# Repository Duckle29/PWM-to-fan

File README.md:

# PWM-to-fan

This is a small board intended to take an open-drain inverted PWM output, and convert it to constant current from 0-200mA for a fan. 
This is because many fans do not run well with their main supply PWMed. The reason to go for Constant current, is to limit the heat wasted in the transistor.

The board was made for use with the Duet 3D printer controllers, but will work for any open-drain inverted PWM outputs.

Many thanks to [N2](http://ee.david.promo) who came up with the circuit.

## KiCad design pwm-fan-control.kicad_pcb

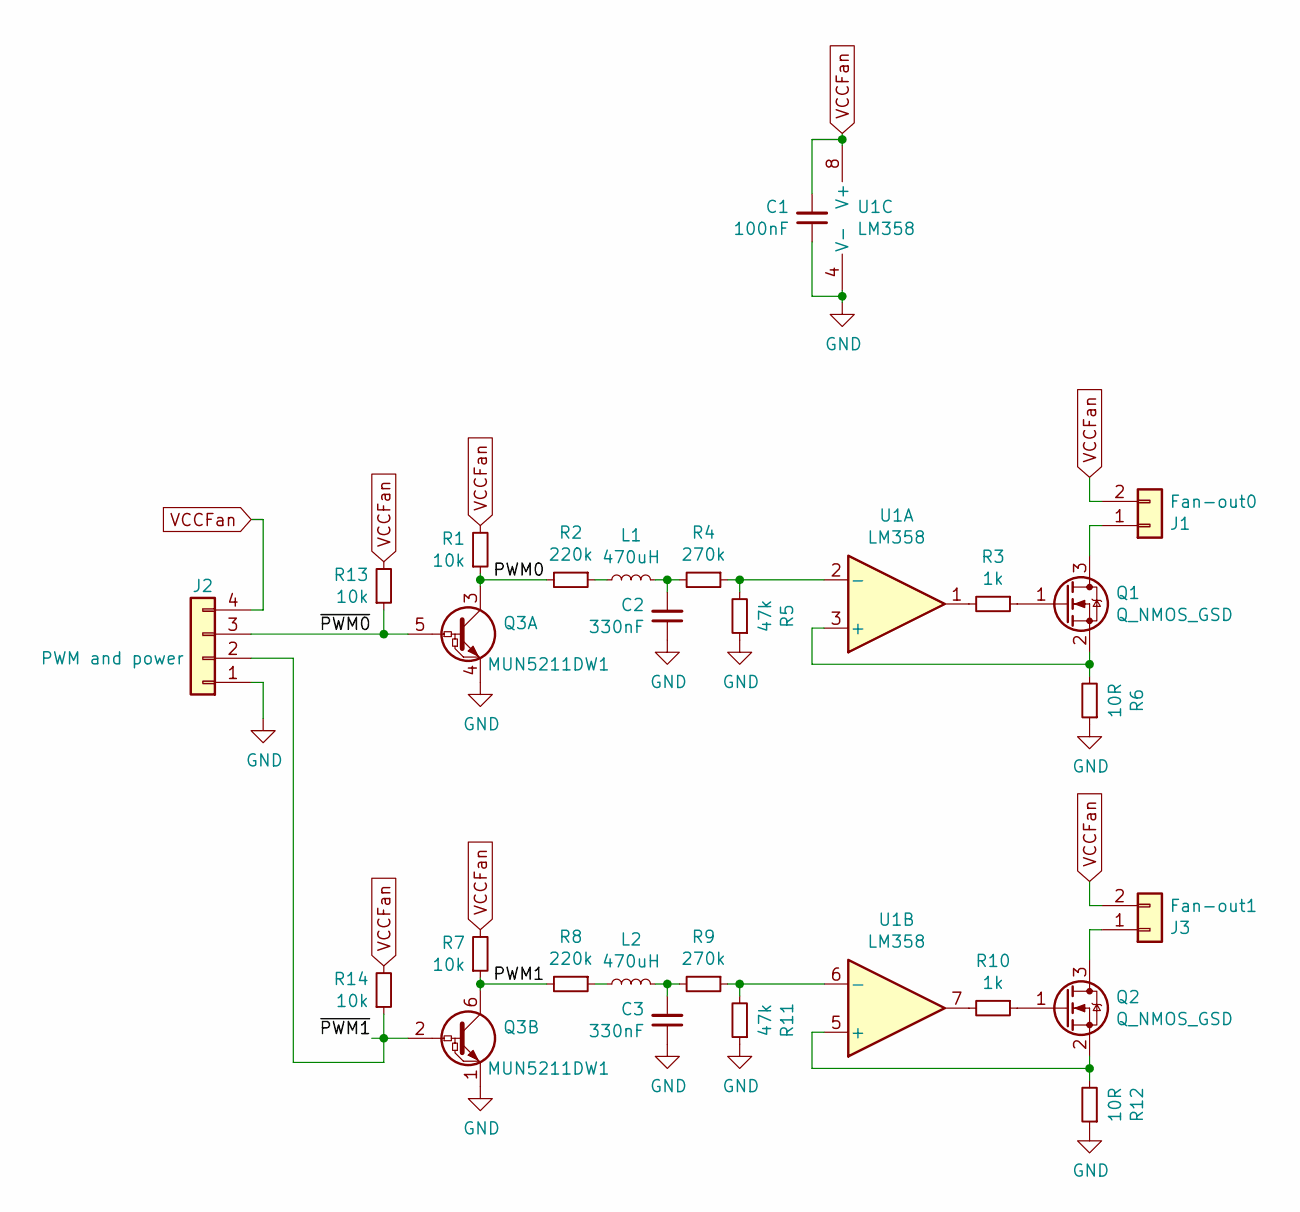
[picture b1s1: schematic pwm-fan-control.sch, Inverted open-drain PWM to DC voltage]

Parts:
C1: 100nF; C_0603_1608Metric_Pad1.05x0.95mm_HandSolder
C2, C3: 330nF; C_0603_1608Metric_Pad1.05x0.95mm_HandSolder
J1: Fan-out0; FanPinHeader_1x03_P2.54mm_Vertical
J2: PWM and power; PinHeader_1x04_P2.54mm_Vertical
J3: Fan-out1; FanPinHeader_1x03_P2.54mm_Vertical
L1, L2: 470uH; L_1210_3225Metric_Pad1.42x2.65mm_HandSolder
Q1, Q2: Q_NMOS_GSD; TO-252-2
Q3: MUN5211DW1; SOT-363_SC-70-6
R1, R7, R13, R14: 10k; R_0603_1608Metric_Pad1.05x0.95mm_HandSolder
R2, R8: 220k; R_0603_1608Metric_Pad1.05x0.95mm_HandSolder
R3, R10: 1k; R_0603_1608Metric_Pad1.05x0.95mm_HandSolder
R4, R9: 270k; R_0603_1608Metric_Pad1.05x0.95mm_HandSolder
R5, R11: 47k; R_0603_1608Metric_Pad1.05x0.95mm_HandSolder
R6, R12: 10R; R_1206_3216Metric_Pad1.42x1.75mm_HandSolder
U1: LM358; SOIC-8_3.9x4.9mm_P1.27mm

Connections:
/PWM0: Q3.3 (C1), R1.1, R2.2
/PWM1: Q3.6 (C1), R7.1, R8.2
/~PWM0: J2.3, Q3.5 (B1), R13.1
/~PWM1: J2.2, Q3.2 (B1), R14.1
GND: C1.1, C2.1, C3.1, J2.1, Q3.1 (E1), Q3.4 (E1), R5.1, R6.1, R11.1, R12.1, U1.4 (V-)
unnamed: C2.2, L1.2, R4.2
unnamed: C3.2, L2.2, R9.2
unnamed: J1.1, Q1.3 (D)
unnamed: J3.1, Q2.3 (D)
unnamed: L1.1, R2.1
unnamed: L2.1, R8.1
unnamed: Q1.1 (G), R3.1
unnamed: Q1.2 (S), R6.2, U1.3 (+)
unnamed: Q2.1 (G), R10.1
unnamed: Q2.2 (S), R12.2, U1.5 (+)
unnamed: R3.2, U1.1
unnamed: R4.1, R5.2, U1.2 (-)
unnamed: R10.2, U1.7
unnamed: R9.1, R11.2, U1.6 (-)
VCCFan: C1.2, J1.2, J2.4, J3.2, R1.2, R7.2, R13.2, R14.2, U1.8 (V+)

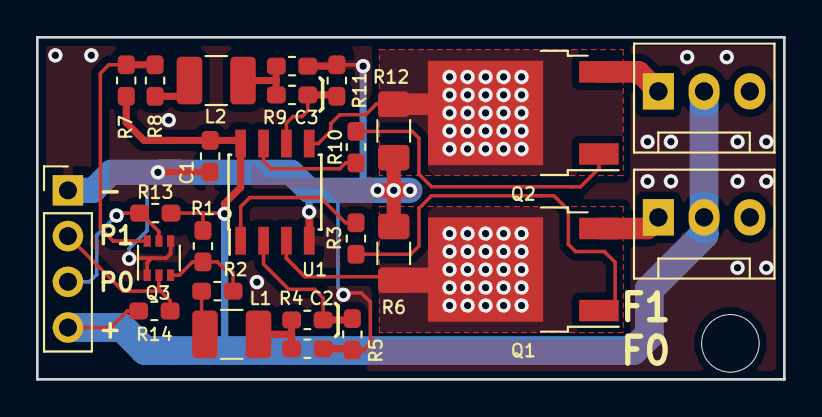
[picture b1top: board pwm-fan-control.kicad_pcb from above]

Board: 2 copper layers, 41.5 x 19.0 mm, 26 parts (0 on the bottom side), 20 nets.

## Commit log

2018-10-12 Added all the files
2018-10-12 Removed "whitespace"
2018-10-12 file jiggling to update images on github
2018-10-12 jigglign back
2018-10-12 Leaving them jiggled
2018-10-12 Added schematic
2018-10-12 More jiggling
2018-10-12 improved bird, added silscreen to the back
2018-10-12 Added link to readme
2018-10-12 Updated image links in readme
2018-10-12 Updated bot image. Pour had rendered weird
2018-10-12 Updated gerbers
2018-10-12 The wizard (N2) came up with a current control scheme instead
2018-10-12 Increased vias on power resistors
2018-10-12 Added dimensions to PCB
2018-10-12 Flipped some stuff for symetry
2018-10-14 Un-inverted PWM input
2018-10-14 Added model-numer to output transistors
2018-10-15 Create LICENSE
